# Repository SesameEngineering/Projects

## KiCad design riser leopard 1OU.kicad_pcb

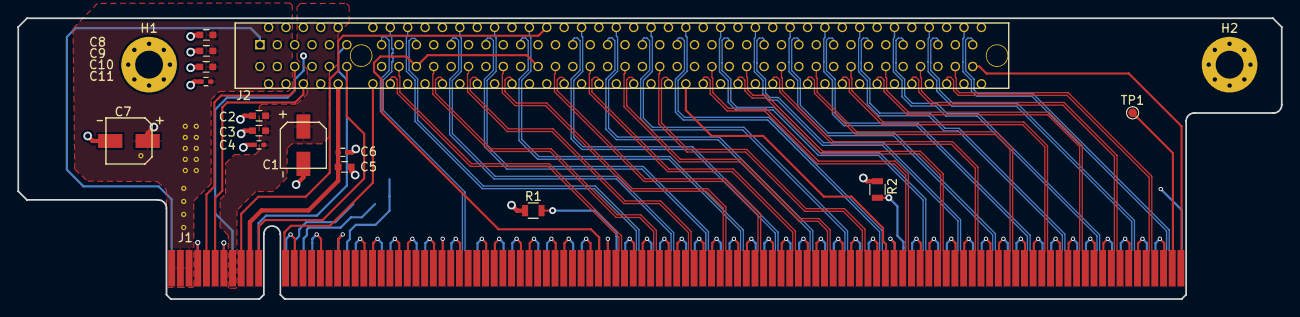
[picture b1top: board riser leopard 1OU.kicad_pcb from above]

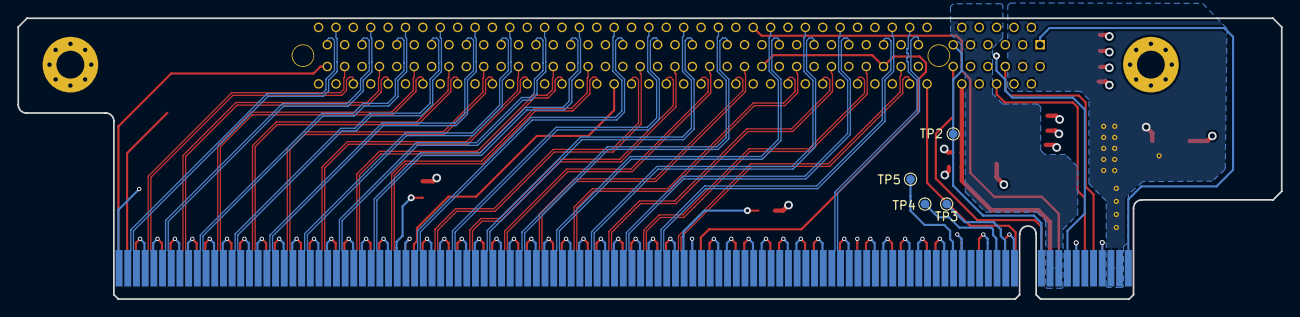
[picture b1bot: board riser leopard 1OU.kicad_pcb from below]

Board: 4 copper layers, 145.4 x 32.3 mm, 22 parts (4 on the bottom side), 87 nets.

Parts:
C1, C7: 100u 16V; CapaElec_100u_16V_5.3mm
C2, C3, C5: 1u 10V; C_0603
C4, C6: 0.1u 10V; C_0402
C8, C9, C10: 1u 25V; C_0603
C11: 0.1u 25V; C_0402
H1, H2: MountingHole_Pad; MountingHole_3.2mm_M3_Pad_Via
J1: CONN_PCIE_x24; pads_pcie_x24
J2: connector_pcie16x; pcie_16x
R1, R2: 0; R_0805
TP1: TP1; TestPoint_Pad_D1.0mm
TP2: TP2; TestPoint_Pad_D1.0mm
TP3: TP3; TestPoint_Pad_D1.0mm
TP4: TP4; TestPoint_Pad_D1.0mm
TP5: TP5; TestPoint_Pad_D1.0mm

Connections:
+3.3Vaux: C5.1, C6.1, J1.B10, J2.B10
+3V3: C1.1, C2.1, C3.1, C4.1, J1.A9, J1.A10, J1.B8, J2.A9, J2.A10, J2.B8
+12V: C7.1, C8.1, C9.1, C10.1, C11.1, J1.A2, J1.A3, J1.B1, J1.B2, J1.B3, J2.A2, J2.A3, J2.B1, J2.B2, J2.B3
/CPU0_RX0+: J1.A52, J2.A16
/CPU0_RX0-: J1.A53, J2.A17
/CPU0_RX1+: J1.A56, J2.A21
/CPU0_RX1-: J1.A57, J2.A22
/CPU0_RX2+: J1.A60, J2.A25
/CPU0_RX2-: J1.A61, J2.A26
/CPU0_RX3+: J1.A64, J2.A29
/CPU0_RX3-: J1.A65, J2.A30
/CPU0_RX4+: J1.A68, J2.A35
/CPU0_RX4-: J1.A69, J2.A36
/CPU0_RX5+: J1.A72, J2.A39
/CPU0_RX5-: J1.A73, J2.A40
/CPU0_RX6+: J1.A76, J2.A43
/CPU0_RX6-: J1.A77, J2.A44
/CPU0_RX7+: J1.A80, J2.A47
/CPU0_RX7-: J1.A81, J2.A48
/CPU0_RX8+: J1.A85, J2.A52
/CPU0_RX8-: J1.A86, J2.A53
/CPU0_RX9+: J1.A89, J2.A56
/CPU0_RX9-: J1.A90, J2.A57
/CPU0_RX10+: J1.A93, J2.A60
/CPU0_RX10-: J1.A94, J2.A61
/CPU0_RX11+: J1.A97, J2.A64
/CPU0_RX11-: J1.A98, J2.A65
/CPU0_RX12+: J1.A101, J2.A68
/CPU0_RX12-: J1.A102, J2.A69
/CPU0_RX13+: J1.A105, J2.A72
/CPU0_RX13-: J1.A106, J2.A73
/CPU0_RX14+: J1.A109, J2.A76
/CPU0_RX14-: J1.A110, J2.A77
/CPU0_RX15+: J1.A113, J2.A80
/CPU0_RX15-: J1.A114, J2.A81
/CPU0_TX0+: J1.B50, J2.B14
/CPU0_TX0-: J1.B51, J2.B15
/CPU0_TX1+: J1.B54, J2.B19
/CPU0_TX1-: J1.B55, J2.B20
/CPU0_TX2+: J1.B58, J2.B23
/CPU0_TX2-: J1.B59, J2.B24
/CPU0_TX3+: J1.B62, J2.B27
/CPU0_TX3-: J1.B63, J2.B28
/CPU0_TX4+: J1.B66, J2.B33
/CPU0_TX4-: J1.B67, J2.B34
/CPU0_TX5+: J1.B70, J2.B37
/CPU0_TX5-: J1.B71, J2.B38
/CPU0_TX6+: J1.B74, J2.B41
/CPU0_TX6-: J1.B75, J2.B42
/CPU0_TX7+: J1.B78, J2.B45
/CPU0_TX7-: J1.B79, J2.B46
/CPU0_TX8+: J1.B83, J2.B50
/CPU0_TX8-: J1.B84, J2.B51
/CPU0_TX9+: J1.B87, J2.B54
/CPU0_TX9-: J1.B88, J2.B55
/CPU0_TX10+: J1.B91, J2.B58
/CPU0_TX10-: J1.B92, J2.B59
/CPU0_TX11+: J1.B95, J2.B62
/CPU0_TX11-: J1.B96, J2.B63
/CPU0_TX12+: J1.B99, J2.B66
/CPU0_TX12-: J1.B100, J2.B67
/CPU0_TX13+: J1.B103, J2.B70
/CPU0_TX13-: J1.B104, J2.B71
/CPU0_TX14+: J1.B107, J2.B74
/CPU0_TX14-: J1.B108, J2.B75
/CPU0_TX15+: J1.B111, J2.B78
/CPU0_TX15-: J1.B112, J2.B79
/IRQ_LVC_WAKE_N: J1.B11, J2.B11
/LAN_SMB_ALERT_N: J1.B12, J2.B12
/LAN_SMB_CLK: J1.B9, J2.A32
/LAN_SMB_DAT: J1.A8, J2.A33
/PCIE_SLOT_PRSNT#1: J1.A1, J2.A1
/PCIE_SLOT_PRSNT_x1x4: J1.B48, J2.B17, J2.B31
/PCIE_SLOT_PRSNT_x8: J1.B81, J2.B48
/PCIE_SLOT_PRSNT_x16: J1.B115, J2.B81
/REF_CLK+: J1.A32, J2.A13
/REF_CLK-: J1.A33, J2.A14
/RST_PERST0_N: J1.A11, J2.A11, TP2.1
/SLOT0_CONFIG: J1.A50, R1.2
/SLOT1_CONFIG: J1.A83, R2.2
/SMB_CLK: J1.B5, J2.B5
/SMB_DATA: J1.B6, J2.B6
GND: C1.2, C2.2, C3.2, C4.2, C5.2, C6.2, C7.2, C8.2, C9.2, C10.2, C11.2, H1.1, H2.1, J1.A4, J1.A7, J1.A12, J1.A15, J1.A18, J1.A20, J1.A23, J1.A24, J1.A27, J1.A28, J1.A31, J1.A34, J1.A37, J1.A38, J1.A41, J1.A42, J1.A45, J1.A46, J1.A49, J1.A51, J1.A54, J1.A55, J1.A58, J1.A59, J1.A62, J1.A63, J1.A66, J1.A67, J1.A70, J1.A71, J1.A74, J1.A75, J1.A78, J1.A79, J1.A82, J1.A84, J1.A87, J1.A88, J1.A91, J1.A92, J1.A95, J1.A96, J1.A99, J1.A100, J1.A103, J1.A104, J1.A107, J1.A108, J1.A111, J1.A112, J1.A115, J1.B4, J1.B7, J1.B13, J1.B16, J1.B18, J1.B21, J1.B22, J1.B25, J1.B26, J1.B29, J1.B30, J1.B32, J1.B35, J1.B36, J1.B39, J1.B40, J1.B43, J1.B44, J1.B47, J1.B49, J1.B52, J1.B53, J1.B56, J1.B57, J1.B60, J1.B61, J1.B64, J1.B65, J1.B68, J1.B69, J1.B72, J1.B73, J1.B76, J1.B77, J1.B80, J1.B82, J1.B85, J1.B86, J1.B89, J1.B90, J1.B93, J1.B94, J1.B97, J1.B98, J1.B101, J1.B102, J1.B105, J1.B106, J1.B109, J1.B110, J1.B113, J2.A4, J2.A12, J2.A15, J2.A18, J2.A20, J2.A23, J2.A24, J2.A27, J2.A28, J2.A31, J2.A34, J2.A37, J2.A38, J2.A41, J2.A42, J2.A45, J2.A46, J2.A49, J2.A50, J2.A51, J2.A54, J2.A55, J2.A58, J2.A59, J2.A62, J2.A63, J2.A66, J2.A67, J2.A70, J2.A71, J2.A74, J2.A75, J2.A78, J2.A79, J2.A82, J2.B4, J2.B7, J2.B13, J2.B16, J2.B18, J2.B21, J2.B22, J2.B25, J2.B26, J2.B29, J2.B32, J2.B35, J2.B36, J2.B39, J2.B40, J2.B43, J2.B44, J2.B47, J2.B49, J2.B52, J2.B53, J2.B56, J2.B57, J2.B60, J2.B61, J2.B64, J2.B65, J2.B68, J2.B69, J2.B72, J2.B73, J2.B76, J2.B77, J2.B80, R1.1, R2.1
unnamed: J1.A13, TP3.1
unnamed: J1.A14, TP4.1
unnamed: J1.A19, TP5.1
unnamed: J1.B114, TP1.1
